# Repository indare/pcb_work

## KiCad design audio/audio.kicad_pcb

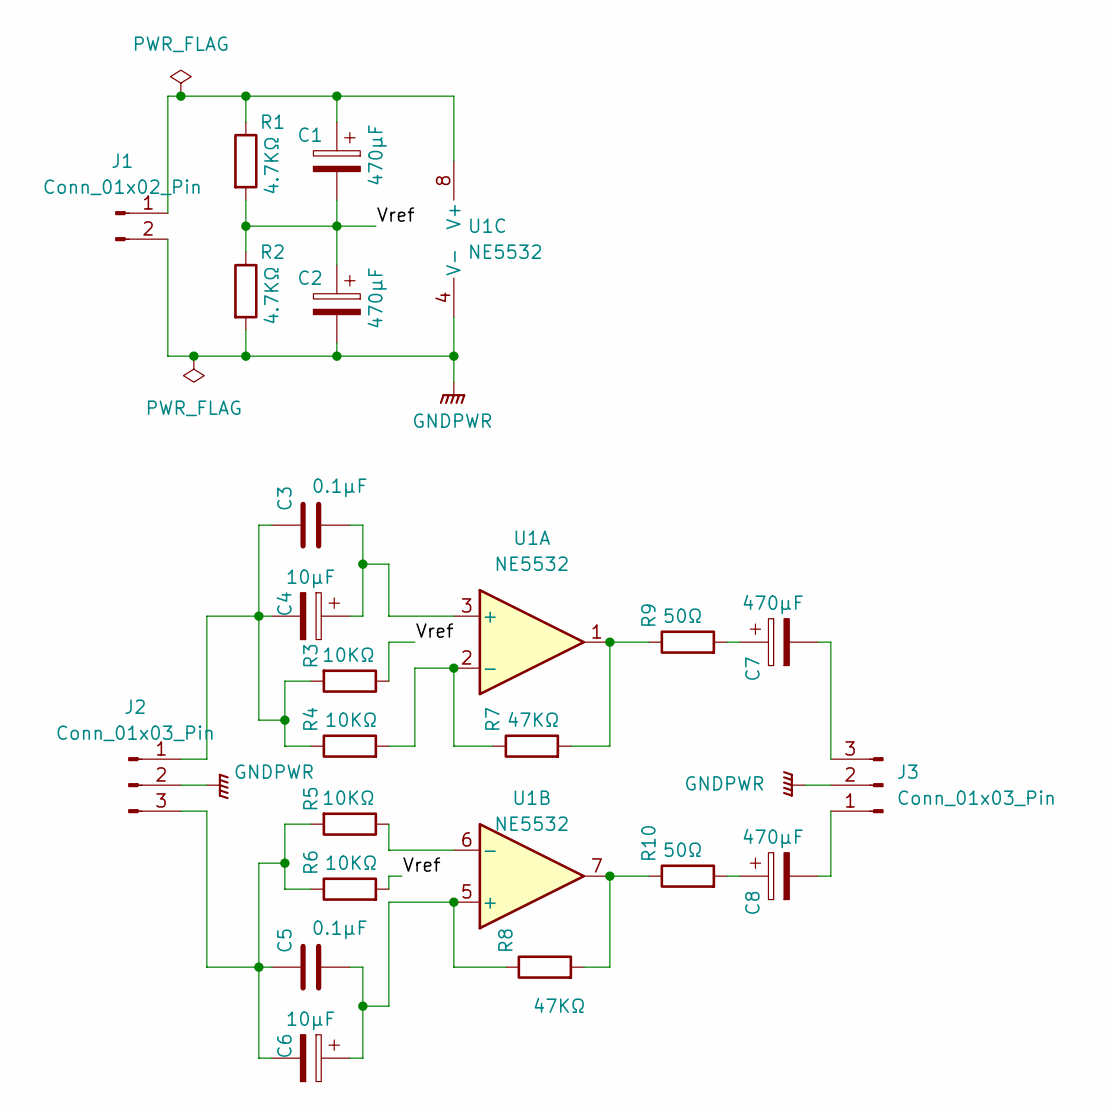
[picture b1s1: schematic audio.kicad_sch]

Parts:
C1, C2, C7, C8: 470μF; CP_Radial_D16.0mm_P7.50mm
C3, C5: 0.1μF; C_Rect_L7.2mm_W2.5mm_P5.00mm_FKS2_FKP2_MKS2_MKP2
C4, C6: 10μF; CP_Radial_D5.0mm_P2.00mm
J1: Conn_01x02_Pin; TerminalBlock_Phoenix_MKDS-1,5-2-5.08_1x02_P5.08mm_Horizont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
J2, J3: Conn_01x03_Pin; TerminalBlock_Phoenix_MKDS-1,5-3_1x03_P5.00mm_Horizontal
R1, R2: 4.7KΩ; R_Axial_DIN0207_L6.3mm_D2.5mm_P10.16mm_Horizontal
R3, R4, R5, R6: 10KΩ; R_Axial_DIN0207_L6.3mm_D2.5mm_P10.16mm_Horizontal
R7, R8: 47KΩ; R_Axial_DIN0207_L6.3mm_D2.5mm_P10.16mm_Horizontal
R9, R10: 50Ω; R_Axial_DIN0207_L6.3mm_D2.5mm_P10.16mm_Horizontal
U1: NE5532; DIP-8_W7.62mm_Socket

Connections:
/Vref: C1.2, C2.1, R1.2, R2.1, R3.1, R6.2
GNDPWR: C2.2, J1.2, J2.2, J3.2, R2.2, U1.4 (V-)
unnamed: C7.1, R9.2
unnamed: C8.1, R10.2
unnamed: C1.1, J1.1, R1.1, U1.8 (V+)
unnamed: C3.2, C4.2, J2.1, R3.2, R4.1
unnamed: C5.2, C6.2, J2.3, R5.2, R6.1
unnamed: C8.2, J3.1
unnamed: C7.2, J3.3
unnamed: R7.2, R9.1, U1.1
unnamed: R8.2, R10.1, U1.7
unnamed: C3.1, C4.1, U1.3 (+)
unnamed: R4.2, R7.1, U1.2 (-)
unnamed: C5.1, C6.1, R8.1, U1.5 (+)
unnamed: R5.1, U1.6 (-)

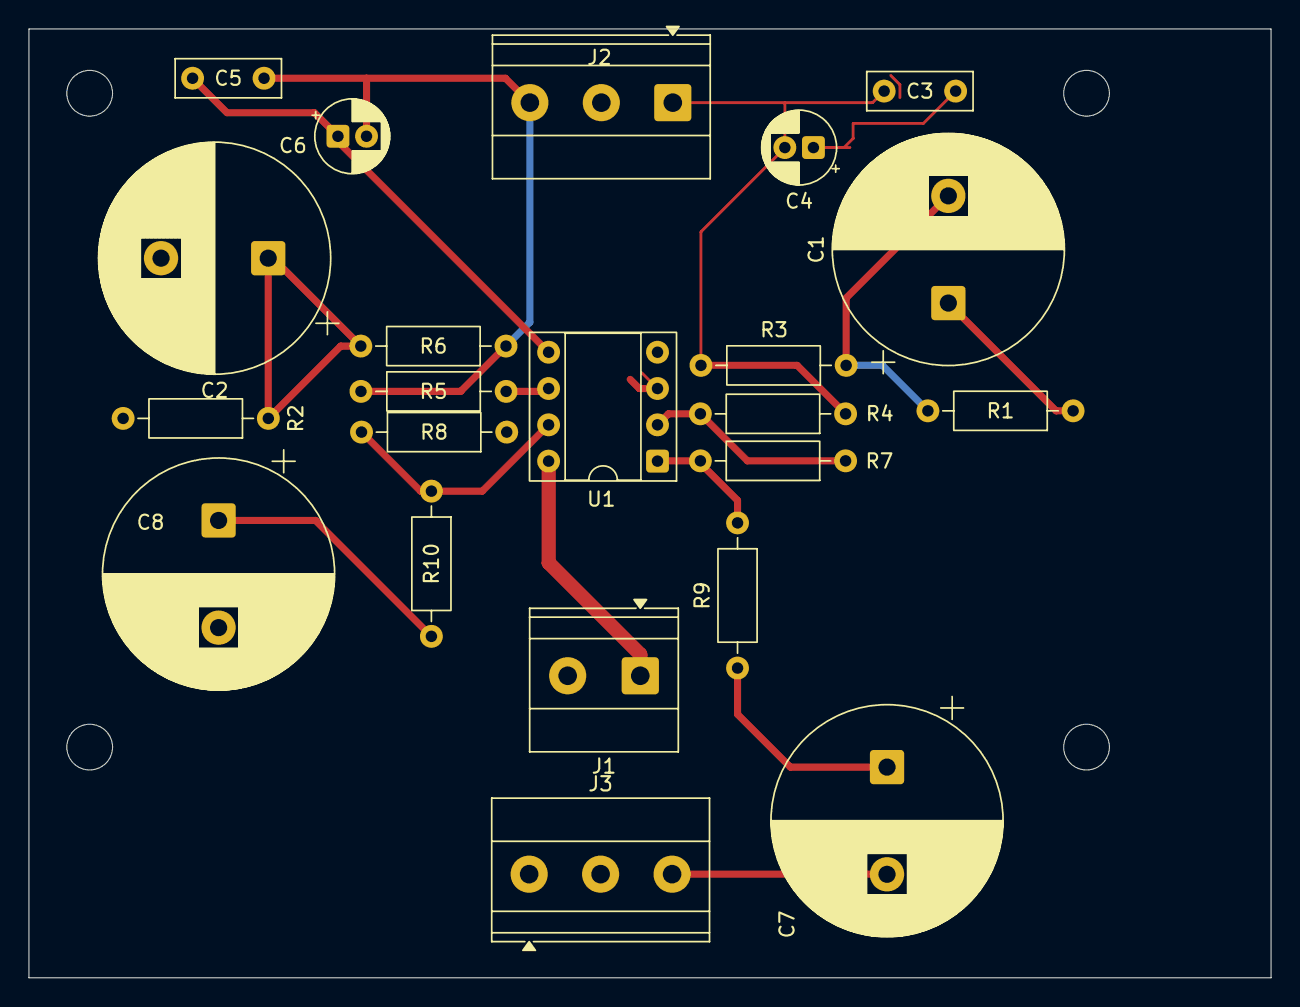
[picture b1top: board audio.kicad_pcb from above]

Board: 2 copper layers, 86.9 x 66.4 mm, 26 parts (0 on the bottom side), 15 nets.

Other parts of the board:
Hole: MountingHole_3.2mm_M3
Hole#2, Hole#3, Hole#4: MountingHole_3.2mm_M3
